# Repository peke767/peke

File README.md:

# peke

## Pocket Keyboard dengan 29 Keys, 28x1u dan 1x2u

## Bahan
- [ ] 1x Pocket PCB
- [ ] 29 1N4148W dioda
- [ ] 1x Pro Micro
- [ ] 29x Switch
- [ ] 28x Keycaps 1u
- [ ] 1x Keycaps 2u
- [ ] 1x Stabilizer Screw-in 2u

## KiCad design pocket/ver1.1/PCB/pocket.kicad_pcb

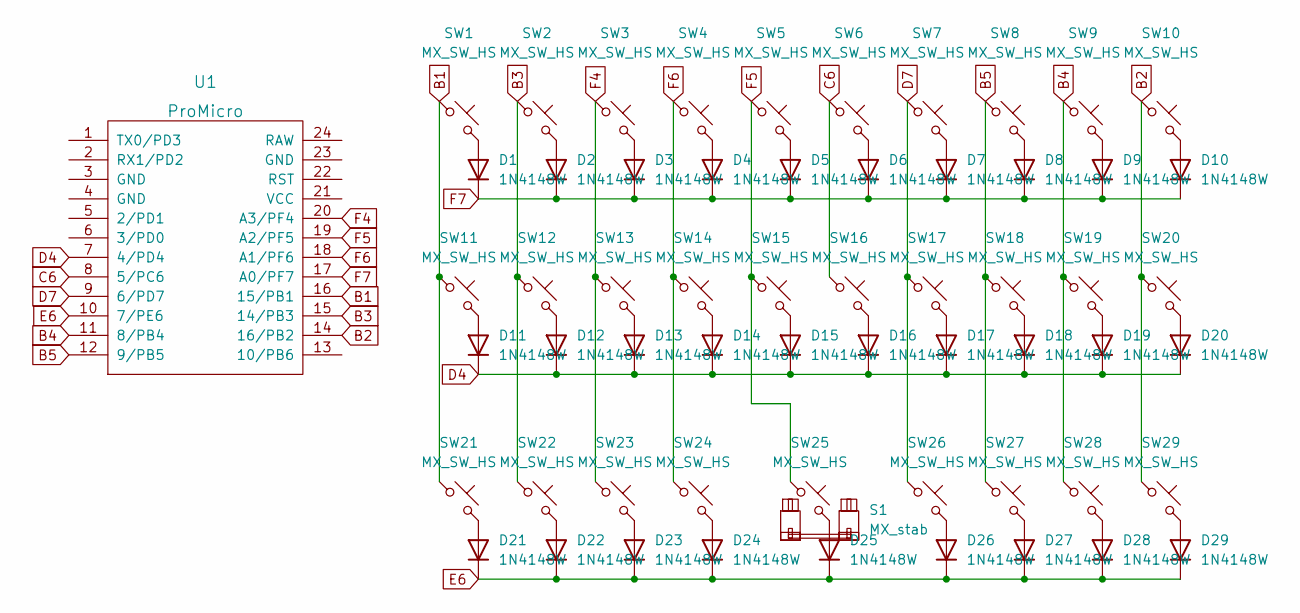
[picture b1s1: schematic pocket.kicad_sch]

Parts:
D1, D2, D3, D4, D5, D6, D7, D8, D9, D10, D11, D12, D13, D14, D15, D16, D17, D18, D19, D20, D21, D22, D23, D24, D25, D26, D27, D28, D29: 1N4148W; D_SOD-123
S1: MX_stab; STAB_MX_2u
SW1, SW2, SW3, SW4, SW5, SW6, SW7, SW8, SW9, SW10, SW11, SW12, SW13, SW14, SW15, SW16, SW17, SW18, SW19, SW20, SW21, SW22, SW23, SW24, SW25, SW26, SW27, SW28, SW29: MX_SW_HS; SW_MX_HS_S_1u
U1: ProMicro; ArduinoProMicro

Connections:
B1: SW1.1, SW11.1, SW21.1, U1.16 (15/PB1)
B2: SW10.1, SW20.1, SW29.1, U1.14 (16/PB2)
B3: SW2.1, SW12.1, SW22.1, U1.15 (14/PB3)
B4: SW9.1, SW19.1, SW28.1, U1.11 (8/PB4)
B5: SW8.1, SW18.1, SW27.1, U1.12 (9/PB5)
C6: SW6.1, SW16.1, U1.8 (5/PC6)
D4: D11.1 (K), D12.1 (K), D13.1 (K), D14.1 (K), D15.1 (K), D16.1 (K), D17.1 (K), D18.1 (K), D19.1 (K), D20.1 (K), U1.7 (4/PD4)
D7: SW7.1, SW17.1, SW26.1, U1.9 (6/PD7)
E6: D21.1 (K), D22.1 (K), D23.1 (K), D24.1 (K), D25.1 (K), D26.1 (K), D27.1 (K), D28.1 (K), D29.1 (K), U1.10 (7/PE6)
F4: SW3.1, SW13.1, SW23.1, U1.20 (A3/PF4)
F5: SW5.1, SW15.1, SW25.1, U1.19 (A2/PF5)
F6: SW4.1, SW14.1, SW24.1, U1.18 (A1/PF6)
F7: D1.1 (K), D2.1 (K), D3.1 (K), D4.1 (K), D5.1 (K), D6.1 (K), D7.1 (K), D8.1 (K), D9.1 (K), D10.1 (K), U1.17 (A0/PF7)
unnamed: D7.2 (A), SW7.2
unnamed: D8.2 (A), SW8.2
unnamed: D10.2 (A), SW10.2
unnamed: D17.2 (A), SW17.2
unnamed: D21.2 (A), SW21.2
unnamed: D25.2 (A), SW25.2
unnamed: D26.2 (A), SW26.2
unnamed: D27.2 (A), SW27.2
unnamed: D1.2 (A), SW1.2
unnamed: D2.2 (A), SW2.2
unnamed: D3.2 (A), SW3.2
unnamed: D4.2 (A), SW4.2
unnamed: D5.2 (A), SW5.2
unnamed: D6.2 (A), SW6.2
unnamed: D9.2 (A), SW9.2
unnamed: D11.2 (A), SW11.2
unnamed: D12.2 (A), SW12.2
unnamed: D13.2 (A), SW13.2
unnamed: D14.2 (A), SW14.2
unnamed: D15.2 (A), SW15.2
unnamed: D16.2 (A), SW16.2
unnamed: D18.2 (A), SW18.2
unnamed: D19.2 (A), SW19.2
unnamed: D20.2 (A), SW20.2
unnamed: D22.2 (A), SW22.2
unnamed: D23.2 (A), SW23.2
unnamed: D24.2 (A), SW24.2
unnamed: D28.2 (A), SW28.2
unnamed: D29.2 (A), SW29.2

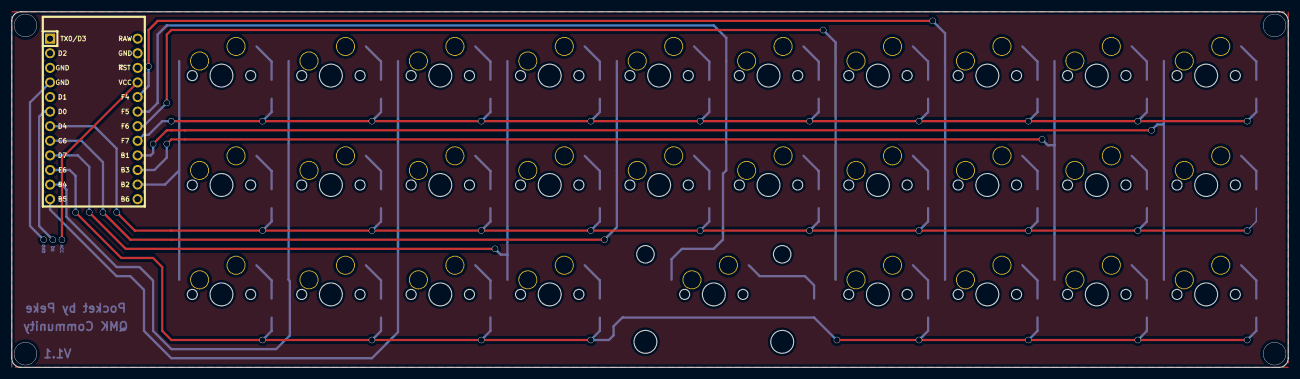
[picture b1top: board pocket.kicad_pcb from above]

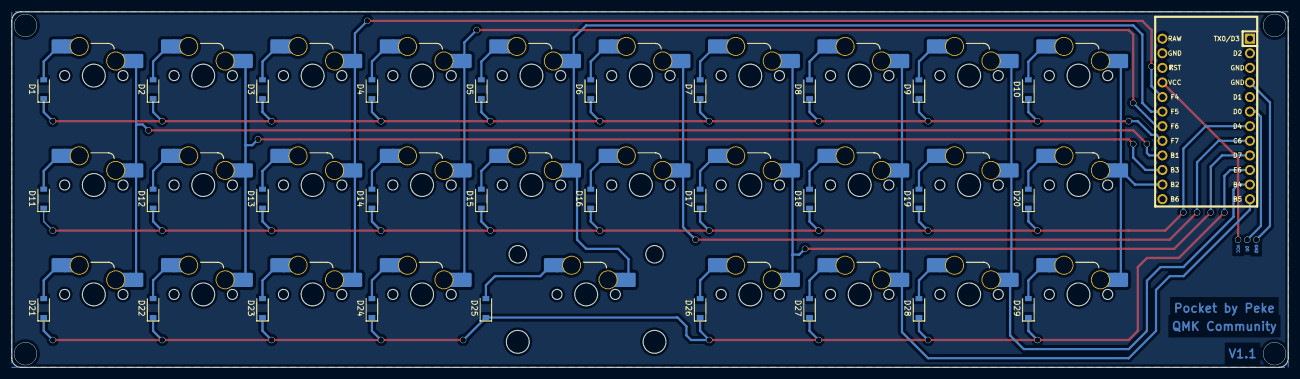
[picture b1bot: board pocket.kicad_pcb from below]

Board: 2 copper layers, 222.2 x 61.9 mm, 60 parts (59 on the bottom side), 42 nets.
